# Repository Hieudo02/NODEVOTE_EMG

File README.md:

V2 là bản Node nút vuông, V3 là bản Node nút tròn.
GW ở V3 dùng được cho Node ở cả V2 và V3

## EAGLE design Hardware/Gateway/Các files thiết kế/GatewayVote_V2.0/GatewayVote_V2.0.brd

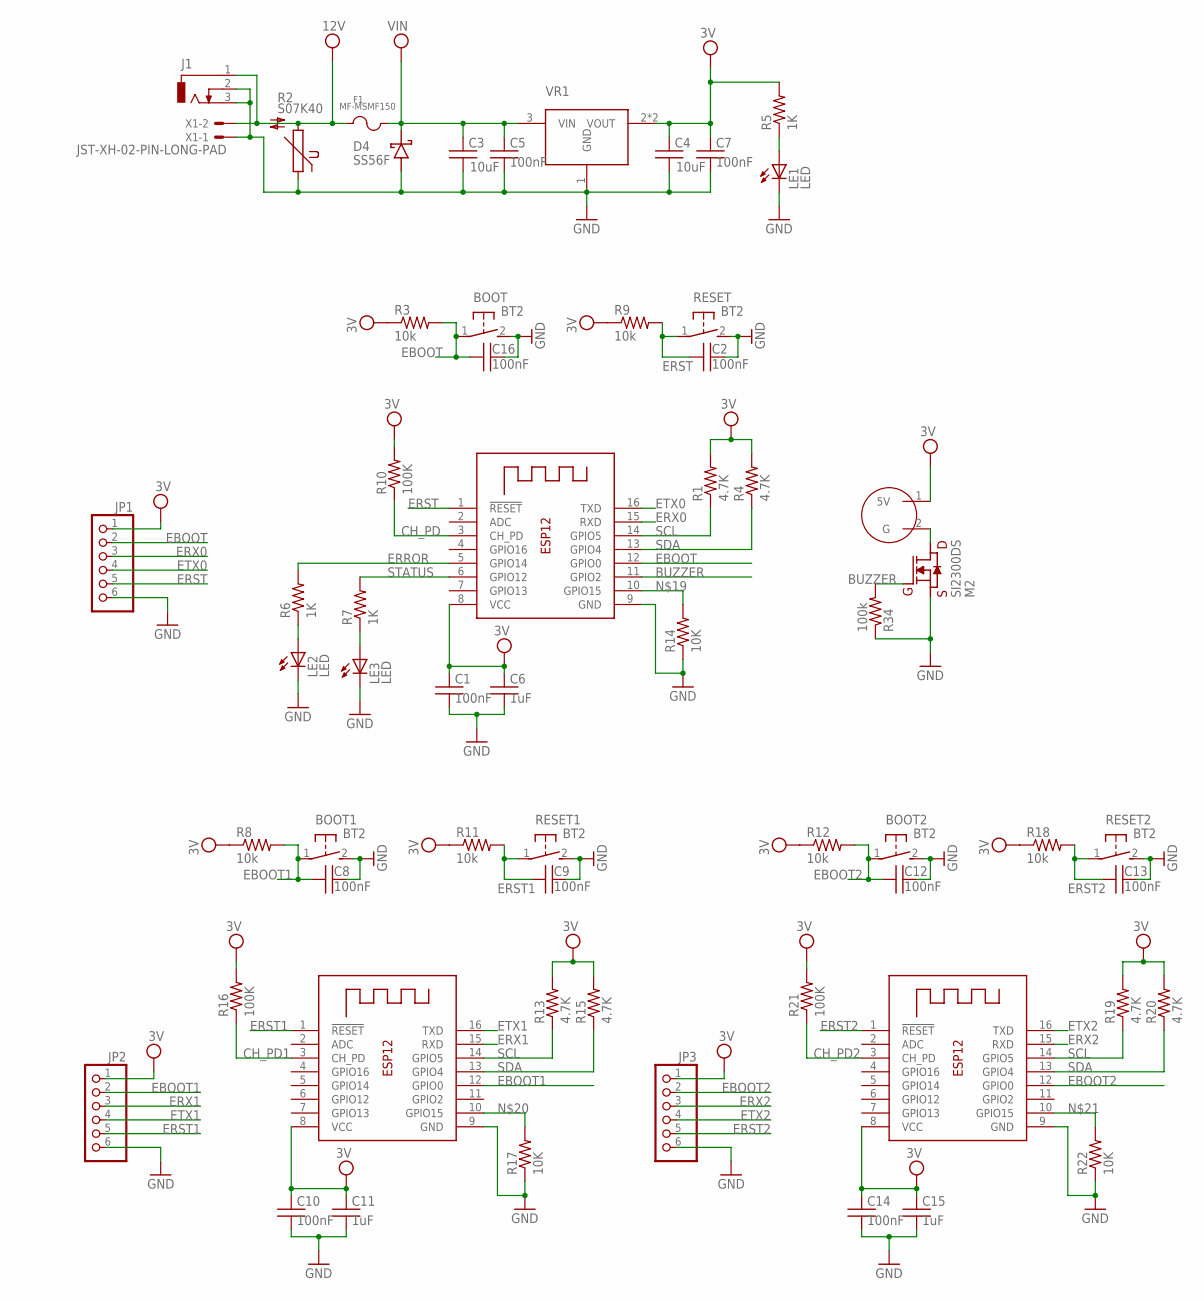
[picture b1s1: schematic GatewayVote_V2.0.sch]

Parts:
BOOT, BOOT1, BOOT2: BT2
C1, C2, C5, C7, C8, C9, C10, C12, C13, C14, C16: 100nF; 0603
C3, C4: 10uF; 0603
C6, C11, C15: 1uF; 0603
D4: SS56F; SMB
F1: MF-MSMF150; FUSER_MF-MSMF150
J1: DCJ0303
JP1, JP2, JP3: PINHD-1X6; 1X06
LE1, LE2, LE3: LED; LED3MM
M2: SI2300DS; SOT23(1)
R1, R4, R13, R15, R19, R20: 4.7K; 0603
R2: S07K40
R3, R8, R9, R11, R12, R18: 10k; 0603
R5, R6, R7: 1K; 0603
R10, R16, R21: 100K; 0603
R14, R17, R22: 10K; 0603
R34: 100k; 0603
RESET, RESET1, RESET2: BT2
U$3: BUZZER-5V
VR1: LD1085D2M33R; VREG_LD1085D2M33R
X1: JST-XH-02-PIN-LONG-PAD; JST-XH-02-PACKAGE-LONG-PAD
X2, X3, X4: ESP-12

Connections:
3V: C1.1, C4.1, C6.1, C7.1, C10.1, C11.1, C14.1, C15.1, JP1.1, JP2.1, JP3.1, R1.2, R3.1, R4.2, R5.2, R8.1, R9.1, R10.2, R11.1, R12.1, R13.2, R15.2, R16.2, R18.1, R19.2, R20.2, R21.2, U$3.1 (5V), VR1.2 (VOUT), VR1.4 (VOUT), X2.8 (VCC), X3.8 (VCC), X4.8 (VCC)
12V: F1.1, J1.1, R2.2, X1.2
BUZZER: M2.1 (G), R34.2, X2.11 (GPIO2)
CH_PD: R10.1, X2.3 (CH_PD)
CH_PD1: R16.1, X3.3 (CH_PD)
CH_PD2: R21.1, X4.3 (CH_PD)
EBOOT: BOOT.1, C16.1, JP1.2, R3.2, X2.12 (GPIO0)
EBOOT1: BOOT1.1, C8.1, JP2.2, R8.2, X3.12 (GPIO0)
EBOOT2: BOOT2.1, C12.1, JP3.2, R12.2, X4.12 (GPIO0)
ERROR: R6.2, X2.5 (GPIO14)
ERST: C2.1, JP1.5, R9.2, RESET.1, X2.1 (!RESET)
ERST1: C9.1, JP2.5, R11.2, RESET1.1, X3.1 (!RESET)
ERST2: C13.1, JP3.5, R18.2, RESET2.1, X4.1 (!RESET)
ERX0: JP1.3, X2.15 (RXD)
ERX1: JP2.3, X3.15 (RXD)
ERX2: JP3.3, X4.15 (RXD)
ETX0: JP1.4, X2.16 (TXD)
ETX1: JP2.4, X3.16 (TXD)
ETX2: JP3.4, X4.16 (TXD)
GND: BOOT.2, BOOT1.2, BOOT2.2, C1.2, C2.2, C3.2, C4.2, C5.2, C6.2, C7.2, C8.2, C9.2, C10.2, C11.2, C12.2, C13.2, C14.2, C15.2, C16.2, D4.A, J1.2, J1.3, JP1.6, JP2.6, JP3.6, LE1.K (C), LE2.K (C), LE3.K (C), M2.2 (S), R2.1, R14.1, R17.1, R22.1, R34.1, RESET.2, RESET1.2, RESET2.2, VR1.1 (GND), X1.1, X2.9 (GND), X3.9 (GND), X4.9 (GND)
unnamed: M2.3 (D), U$3.2 (G)
unnamed: LE2.A, R6.1
unnamed: LE3.A, R7.1
unnamed: R14.2, X2.10 (GPIO15)
unnamed: R17.2, X3.10 (GPIO15)
unnamed: R22.2, X4.10 (GPIO15)
unnamed: LE1.A, R5.1
SCL: R1.1, R13.1, R19.1, X2.14 (GPIO5), X3.14 (GPIO5), X4.14 (GPIO5)
SDA: R4.1, R15.1, R20.1, X2.13 (GPIO4), X3.13 (GPIO4), X4.13 (GPIO4)
STATUS: R7.2, X2.6 (GPIO12)
VIN: C3.1, C5.1, D4.C, F1.2, VR1.3 (VIN)

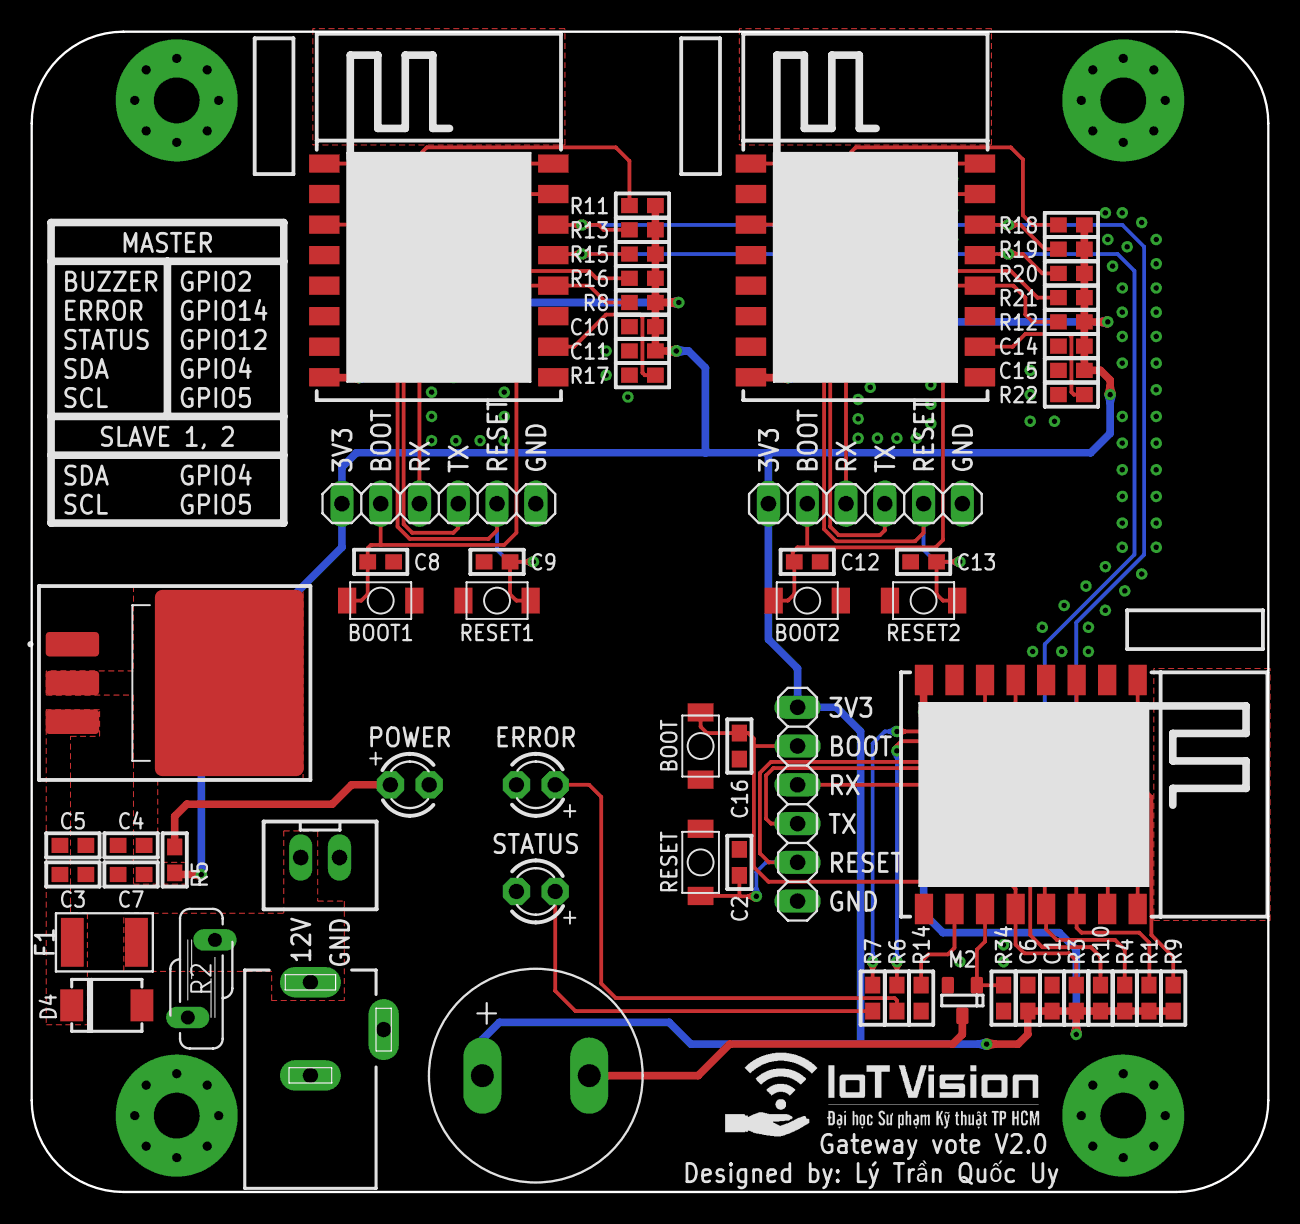
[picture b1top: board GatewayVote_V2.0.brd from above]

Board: 2 copper layers, 81.0 x 76.0 mm, 62 parts (0 on the bottom side), 31 nets.

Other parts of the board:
U$2: 1.2MIL

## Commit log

2024-05-05 Create NodeVote_V2
2024-05-05 V3 NodeVote
2024-05-07 V3 Node Vote (not last version)
